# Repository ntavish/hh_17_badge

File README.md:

PCB Badge for hillhacks 2017
============================

Based around stm32f072 (48 pin) and used capacitive touch footprints from https://github.com/maltman23/ArduTouch/

TODO
----

* add battery connector

* verify crystal loading caps acc. to crystal, rc lpf passives values

* firmware

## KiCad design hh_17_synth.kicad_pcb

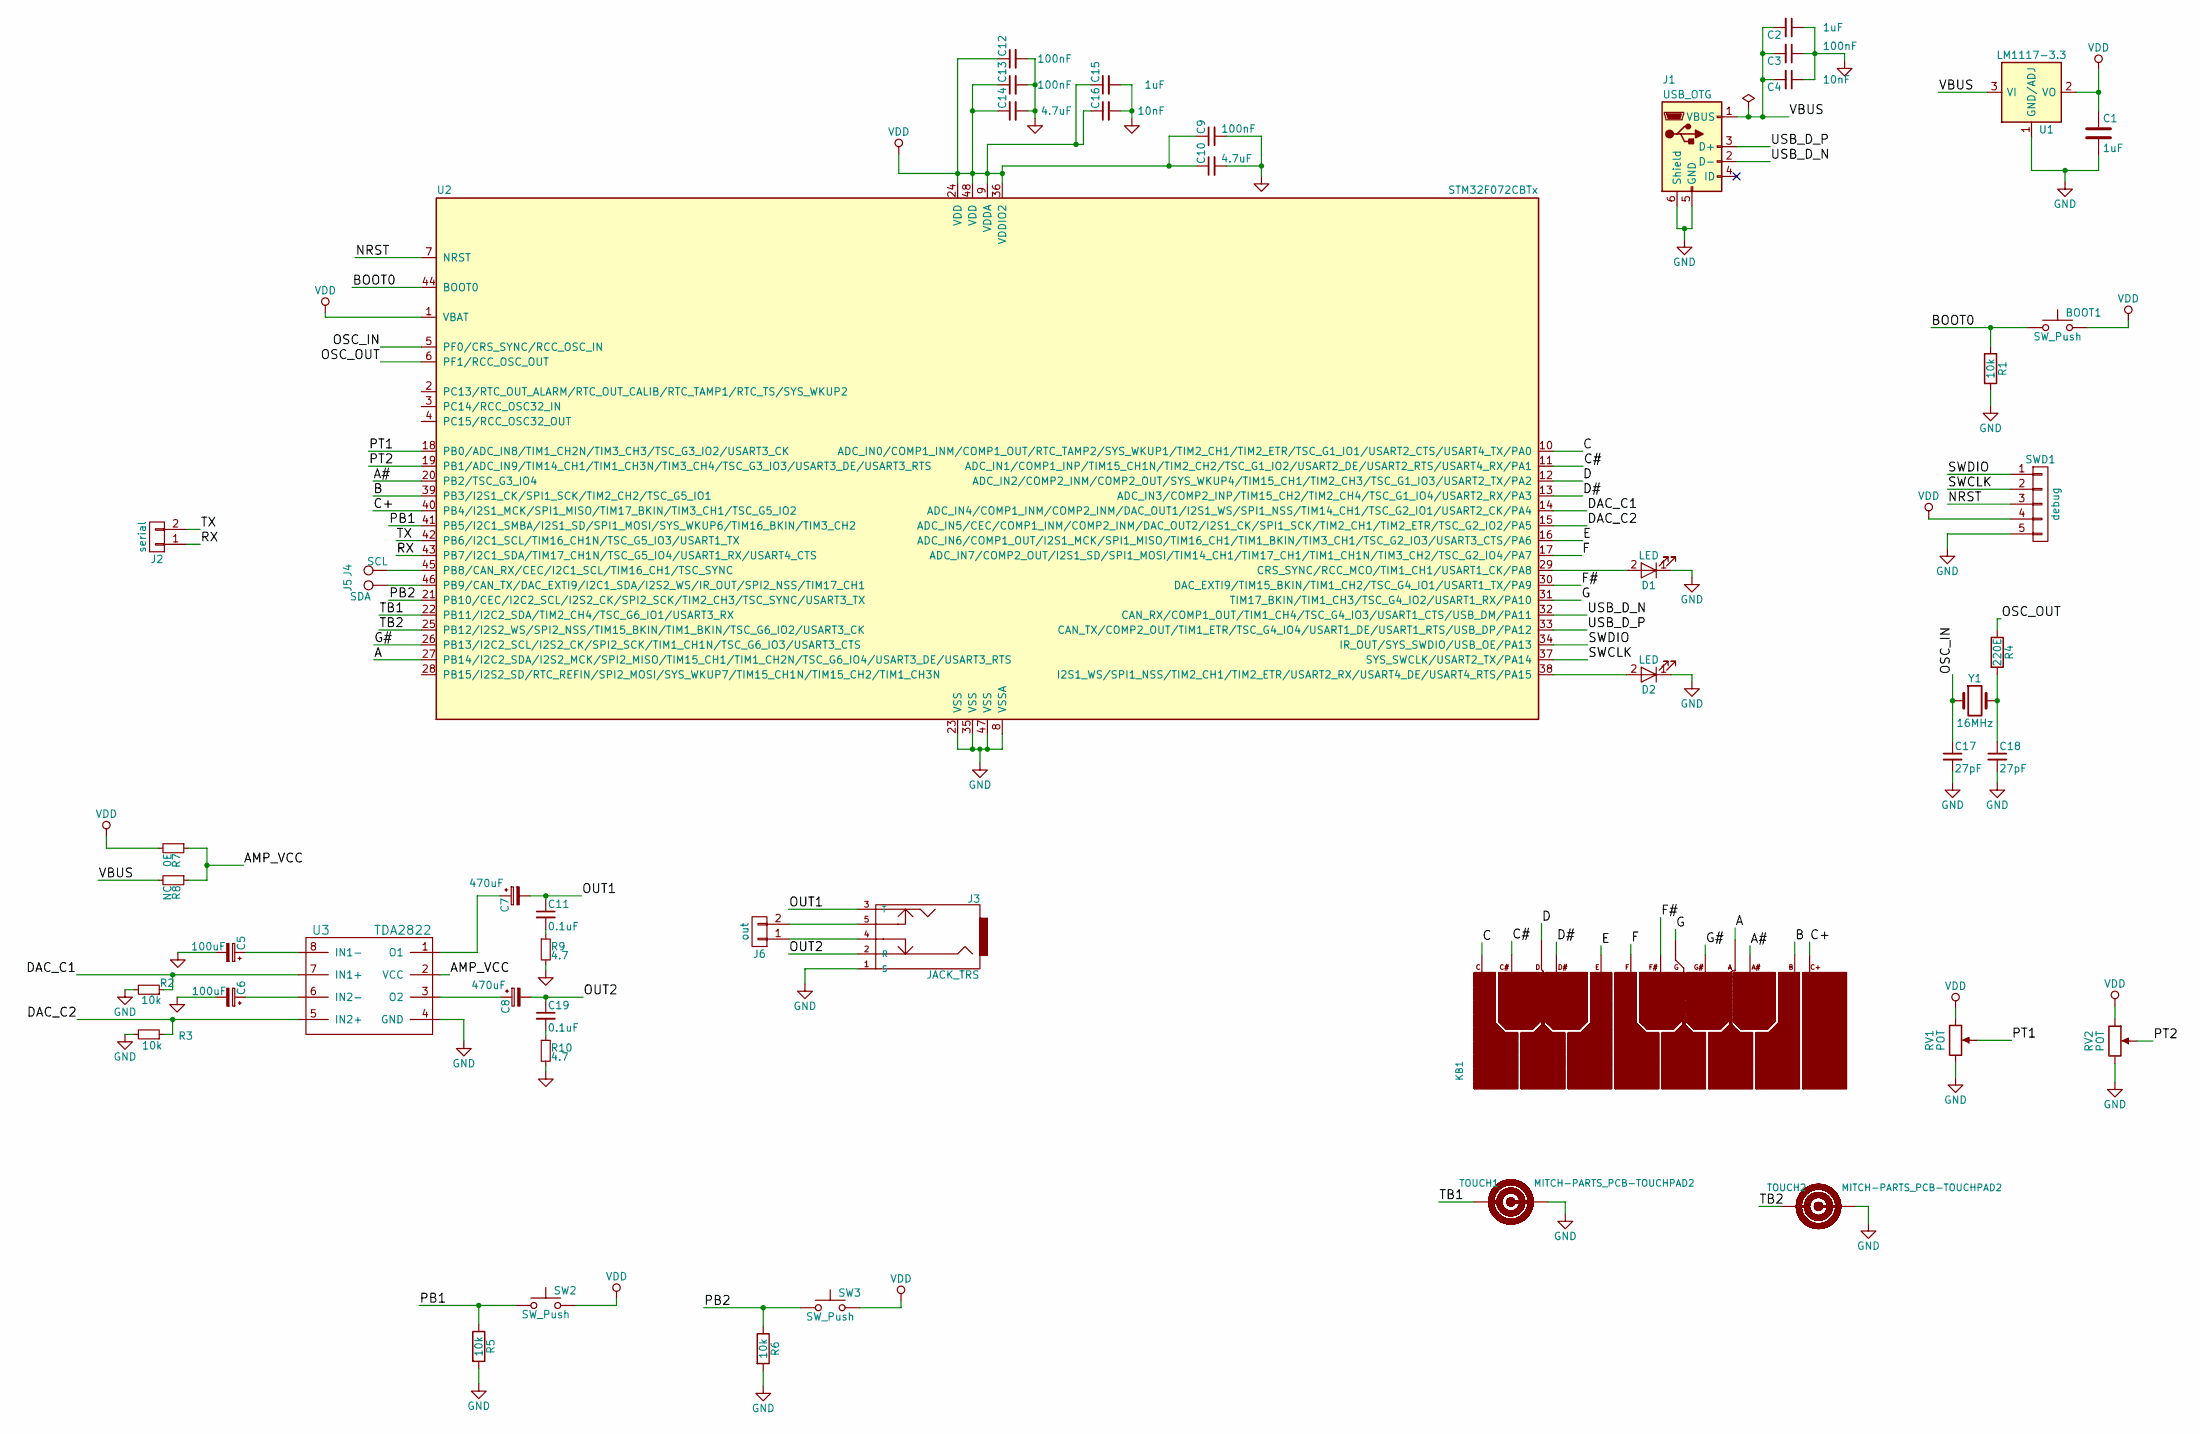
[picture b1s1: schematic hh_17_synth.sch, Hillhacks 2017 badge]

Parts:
BOOT1: SW_Push; SW_PUSH_6mm
C1, C2, C15: 1uF; C_0603
C3, C9, C12, C13: 100nF; C_0603
C4, C16: 10nF; C_0603
C5, C6: 100uF; CP_Radial_D5.0mm_P2.00mm
C7, C8: 470uF; CP_Radial_D5.0mm_P2.00mm
C10, C14: 4.7uF; C_0603
C11, C19: 0.1uF; C_0603
C17, C18: 27pF; C_0603
D1, D2: LED; LED_0603
J1: USB_OTG; HDMI_476420001_CONN
J2: serial; Pin_Header_Straight_1x02_Pitch2.54mm
J3: JACK_TRS; Tayda_3.5mm_stereo_TRS_jack_A-853
J4: SCL; Measurement_Point_Round-SMD-Pad_Small
J5: SDA; Measurement_Point_Round-SMD-Pad_Small
J6: out; Pin_Header_Straight_1x02_Pitch2.54mm
KB1: MITCH-PARTS_PCB-KEYBOARD2; MITCH-PARTS_PCB-KEYBOARD2_kicad_fix
R1, R2, R3, R5, R6: 10k; R_0603
R4: 220E; R_0603
R7: 0E; R_0603
R8: NC; R_0603
R9, R10: 4.7; R_0603
RV1, RV2: POT; 3386P-1-T
SW2, SW3: SW_Push; SW_PUSH_6mm
SWD1: debug; Pin_Header_Straight_1x05_Pitch2.54mm
TOUCH1, TOUCH2: MITCH-PARTS_PCB-TOUCHPAD2; MITCH-PARTS_PCB-TOUCHPAD2_kicad_fix
U1: LM1117-3.3; SOT-223
U2: STM32F072CBTx; LQFP-48_7x7mm_Pitch0.5mm
U3: TDA2822; SOIC-8_3.9x4.9mm_Pitch1.27mm
Y1: 16MHz; Crystal_HC49-4H_Vertical

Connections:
/A: KB1.A, U2.27 (PB14/I2C2_SDA/I2S2_MCK/SPI2_MISO/TIM15_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)
/A#: KB1.A#, U2.20 (PB2/TSC_G3_IO4)
/AMP_VCC: R7.1, R8.1, U3.2 (VCC)
/B: KB1.B, U2.39 (PB3/I2S1_CK/SPI1_SCK/TIM2_CH2/TSC_G5_IO1)
/BOOT0: BOOT1.1, R1.1, U2.44 (BOOT0)
/C: KB1.C, U2.10 (ADC_IN0/COMP1_INM/COMP1_OUT/RTC_TAMP2/S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)
/C#: KB1.C#, U2.11 (ADC_IN1/COMP1_INP/TIM15_CH1N/TIM2_CH2/T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)
/C+: KB1.C+, U2.40 (PB4/I2S1_MCK/SPI1_MISO/TIM17_BKIN/TIM3_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)
/D: KB1.D, U2.12 (ADC_IN2/COMP2_INM/COMP2_OUT/SYS_WKUP4/T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)
/D#: KB1.D#, U2.13 (ADC_IN3/COMP2_INP/TIM15_CH2/TIM2_CH4/TS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)
/DAC_C1: R2.1, U2.14 (ADC_IN4/COMP1_INM/COMP2_INM/DAC_OUT1/I2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), U3.7 (IN1+)
/DAC_C2: R3.1, U2.15 (ADC_IN5/CEC/COMP1_INM/COMP2_INM/DAC_OUT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), U3.5 (IN2+)
/E: KB1.E, U2.16 (ADC_IN6/COMP1_OUT/I2S1_MCK/SPI1_MISO/TI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)
/F: KB1.F, U2.17 (ADC_IN7/COMP2_OUT/I2S1_SD/SPI1_MOSI/TIM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)
/F#: KB1.F#, U2.30 (DAC_EXTI9/TIM15_BKIN/TIM1_CH2/TSC_G4_IO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)
/G: KB1.G, U2.31 (TIM17_BKIN/TIM1_CH3/TSC_G4_IO2/USART1_R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)
/G#: KB1.G#, U2.26 (PB13/I2C2_SCL/I2S2_CK/SPI2_SCK/TIM1_CH1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)
/NRST: SWD1.3, U2.7 (NRST)
/OSC_IN: C17.1, U2.5 (PF0/CRS_SYNC/RCC_OSC_IN), Y1.1
/OSC_OUT: R4.1, U2.6 (PF1/RCC_OSC_OUT)
/OUT1: C7.2, C11.1, J3.3 (T)
/OUT2: C8.2, C19.1, J3.2 (R)
/PB1: R5.1, SW2.1, U2.41 (PB5/I2C1_SMBA/I2S1_SD/SPI1_MOSI/SYS_WKU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)
/PB2: R6.1, SW3.1, U2.21 (PB10/CEC/I2C2_SCL/I2S2_CK/SPI2_SCK/TIM2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)
/PT1: RV1.2, U2.18 (PB0/ADC_IN8/TIM1_CH2N/TIM3_CH3/TSC_G3_I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)
/PT2: RV2.2, U2.19 (PB1/ADC_IN9/TIM14_CH1/TIM1_CH3N/TIM3_CH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)
/RX: J2.1, U2.43 (PB7/I2C1_SDA/TIM17_CH1N/TSC_G5_IO4/USAR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)
/SWCLK: SWD1.2, U2.37 (SYS_SWCLK/USART2_TX/PA14)
/SWDIO: SWD1.1, U2.34 (IR_OUT/SYS_SWDIO/USB_OE/PA13)
/TB1: TOUCH1.1, U2.22 (PB11/I2C2_SDA/TIM2_CH4/TSC_G6_IO1/USART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)
/TB2: TOUCH2.1, U2.25 (PB12/I2S2_WS/SPI2_NSS/TIM15_BKIN/TIM1_B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)
/TX: J2.2, U2.42 (PB6/I2C1_SCL/TIM16_CH1N/TSC_G5_IO3/USAR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)
/USB_D_N: J1.2 (D-), U2.32 (CAN_RX/COMP1_OUT/TIM1_CH4/TSC_G4_IO3/US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)
/USB_D_P: J1.3 (D+), U2.33 (CAN_TX/COMP2_OUT/TIM1_ETR/TSC_G4_IO4/US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)
/VBUS: C2.2, C3.2, C4.2, J1.1 (VBUS), R8.2, U1.3 (VI)
GND: C1.2, C2.1, C3.1, C4.1, C5.2, C6.2, C9.2, C10.2, C12.2, C13.2, C14.2, C15.2, C16.2, C17.2, C18.2, D1.1 (K), D2.1 (K), J1.5 (GND), J1.6 (Shield), J3.1 (S), R1.2, R2.2, R3.2, R5.2, R6.2, R9.2, R10.2, RV1.3, RV2.3, SWD1.5, TOUCH1.2, TOUCH2.2, U1.1 (GND/ADJ), U2.8 (VSSA), U2.23 (VSS), U2.35 (VSS), U2.47 (VSS), U3.4 (GND)
unnamed: C5.1, U3.8 (IN1-)
unnamed: C6.1, U3.6 (IN2-)
unnamed: C7.1, U3.1 (O1)
unnamed: C8.1, U3.3 (O2)
unnamed: C11.2, R9.1
unnamed: C18.1, R4.2, Y1.2
unnamed: C19.2, R10.1
unnamed: D1.2 (A), U2.29 (CRS_SYNC/RCC_MCO/TIM1_CH1/USART1_CK/PA8)
unnamed: D2.2 (A), U2.38 (I2S1_WS/SPI1_NSS/TIM2_CH1/TIM2_ETR/USAR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)
unnamed: J3.4, J6.1
unnamed: J3.5, J6.2
unnamed: J4.1, U2.45 (PB8/CAN_RX/CEC/I2C1_SCL/TIM16_CH1/TSC_S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)
unnamed: J5.1, U2.46 (PB9/CAN_TX/DAC_EXTI9/I2C1_SDA/I2S2_WS/I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)
VDD: BOOT1.2, C1.1, C9.1, C10.1, C12.1, C13.1, C14.1, C15.1, C16.1, R7.2, RV1.1, RV2.1, SW2.2, SW3.2, SWD1.4, U1.2 (VO), U1.4 (VO), U2.1 (VBAT), U2.9 (VDDA), U2.24 (VDD), U2.36 (VDDIO2), U2.48 (VDD)

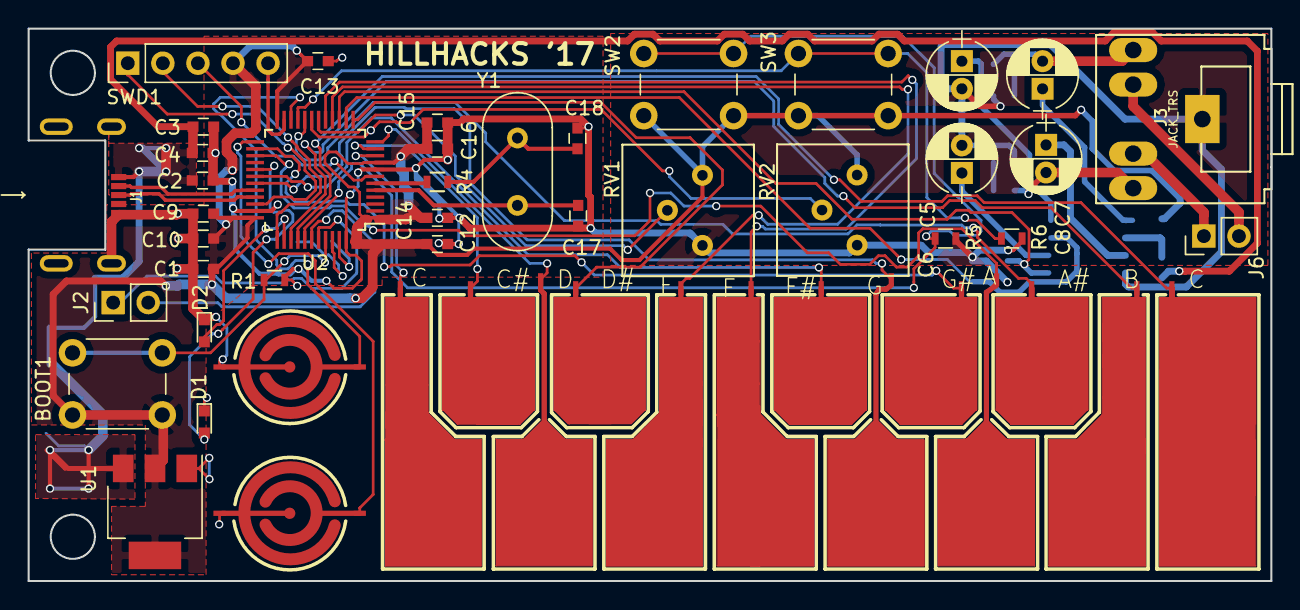
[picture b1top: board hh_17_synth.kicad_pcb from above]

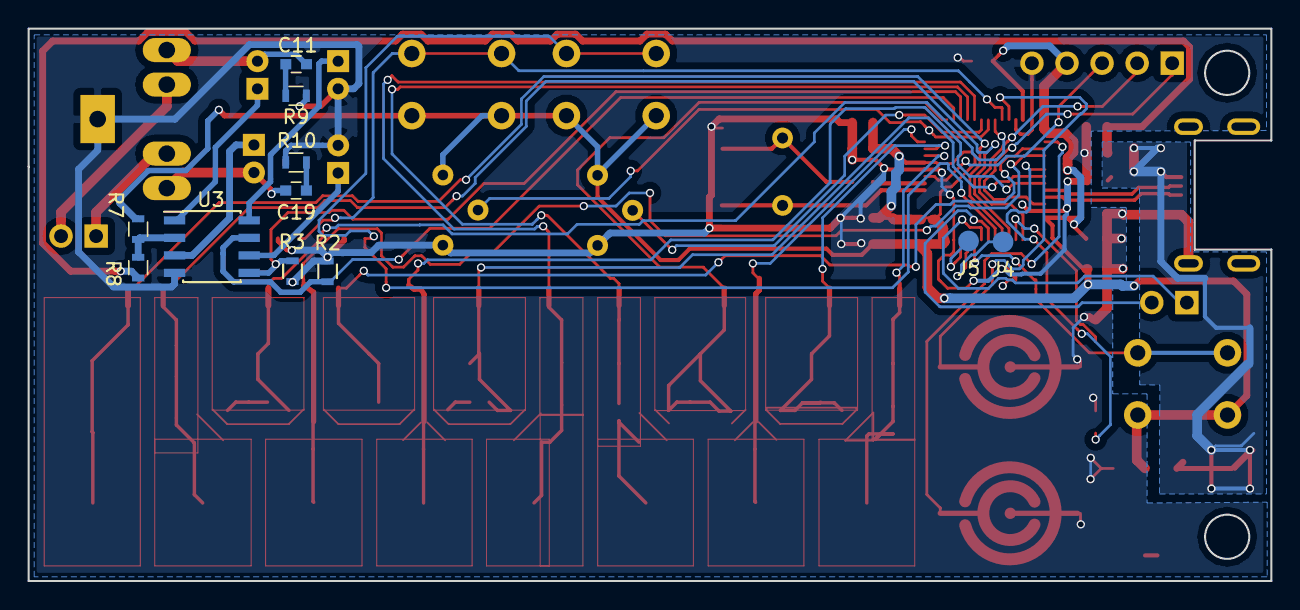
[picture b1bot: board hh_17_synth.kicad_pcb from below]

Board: 2 copper layers, 90.0 x 40.0 mm, 50 parts (11 on the bottom side), 50 nets.

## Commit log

2017-02-17 switch to 48 pin chip, add headphone jack etc.
2017-02-19 Imported Mitch's touchpad and keyboard lib/mod
2017-02-19 placed parts, changed some footprints.
2017-02-19 finished layout etc.
2017-02-19 update todo
2017-02-20 library cleanup and minor changes.
2017-02-20 add readme
2017-03-01 updated layout with buttons/pots
2017-03-01 minor: doc update
2017-03-01 add image
2017-04-23 added audio amp, uart port, leds
2017-04-23 smaller caps remove in-schematic comments updated preview image
2017-04-23 add schematic pdf
2017-04-24 changed uart conn to 2 pin (no gnd) misc layout improvements.
